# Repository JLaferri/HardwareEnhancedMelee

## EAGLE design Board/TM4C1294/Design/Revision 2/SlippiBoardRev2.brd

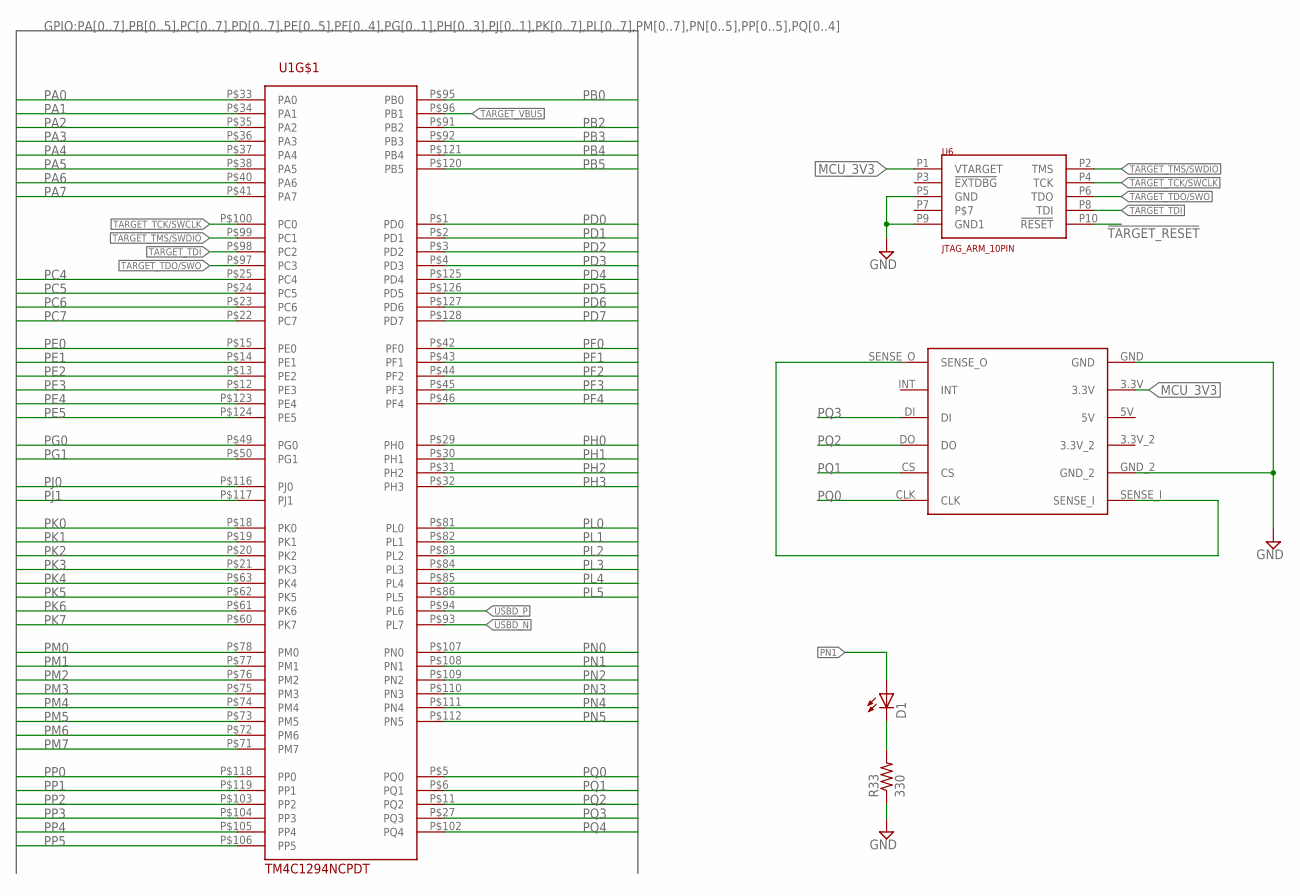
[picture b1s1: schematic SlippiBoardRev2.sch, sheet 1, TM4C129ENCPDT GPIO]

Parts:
D1: LEDCHIPLED_0603; CHIPLED_0603
R33: 330; R0402
U1: TM4C1294NCPDT; TQFP-128
U6: JTAG_ARM_10PIN; CON_2X5_50MIL
U$1: GC_MEMCARD_CON

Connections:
!TARGET_RESET: U6.P10 (!RESET); also elsewhere on the board
GND: R33.1, U6.P5 (GND), U6.P9 (GND1), U$1.GND, U$1.GND_2; also elsewhere on the board
MCU_3V3: U6.P1 (VTARGET), U$1.3.3V; also elsewhere on the board
unnamed: U$1.SENSE_I, U$1.SENSE_O
unnamed: D1.C, R33.2
PA0: U1.P$33 (PA0)
PA1: U1.P$34 (PA1)
PA2: U1.P$35 (PA2)
PA3: U1.P$36 (PA3)
PA4: U1.P$37 (PA4)
PA5: U1.P$38 (PA5)
PA6: U1.P$40 (PA6)
PA7: U1.P$41 (PA7)
PB0: U1.P$95 (PB0)
PB2: U1.P$91 (PB2)
PB3: U1.P$92 (PB3)
PB4: U1.P$121 (PB4)
PB5: U1.P$120 (PB5)
PC4: U1.P$25 (PC4)
PC5: U1.P$24 (PC5)
PC6: U1.P$23 (PC6)
PC7: U1.P$22 (PC7)
PD0: U1.P$1 (PD0)
PD1: U1.P$2 (PD1)
PD2: U1.P$3 (PD2)
PD3: U1.P$4 (PD3)
PD4: U1.P$125 (PD4)
PD5: U1.P$126 (PD5)
PD6: U1.P$127 (PD6)
PD7: U1.P$128 (PD7)
PE0: U1.P$15 (PE0)
PE1: U1.P$14 (PE1)
PE2: U1.P$13 (PE2)
PE3: U1.P$12 (PE3)
PE4: U1.P$123 (PE4)
PE5: U1.P$124 (PE5)
PF0: U1.P$42 (PF0)
PF1: U1.P$43 (PF1)
PF2: U1.P$44 (PF2)
PF3: U1.P$45 (PF3)
PF4: U1.P$46 (PF4)
PG0: U1.P$49 (PG0)
PG1: U1.P$50 (PG1)
PH0: U1.P$29 (PH0)
PH1: U1.P$30 (PH1)
PH2: U1.P$31 (PH2)
PH3: U1.P$32 (PH3)
PJ0: U1.P$116 (PJ0)
PJ1: U1.P$117 (PJ1)
PK0: U1.P$18 (PK0)
PK1: U1.P$19 (PK1)
PK2: U1.P$20 (PK2)
PK3: U1.P$21 (PK3)
PK4: U1.P$63 (PK4)
PK5: U1.P$62 (PK5)
PK6: U1.P$61 (PK6)
PK7: U1.P$60 (PK7)
PL0: U1.P$81 (PL0)
PL1: U1.P$82 (PL1)
PL2: U1.P$83 (PL2)
PL3: U1.P$84 (PL3)
PL4: U1.P$85 (PL4)
PL5: U1.P$86 (PL5)
PM0: U1.P$78 (PM0)
PM1: U1.P$77 (PM1)
PM2: U1.P$76 (PM2)
PM3: U1.P$75 (PM3)
PM4: U1.P$74 (PM4)
PM5: U1.P$73 (PM5)
PM6: U1.P$72 (PM6)
PM7: U1.P$71 (PM7)
PN0: U1.P$107 (PN0)
PN1: D1.A, U1.P$108 (PN1)
PN2: U1.P$109 (PN2)
PN3: U1.P$110 (PN3)
PN4: U1.P$111 (PN4)
PN5: U1.P$112 (PN5)
PP0: U1.P$118 (PP0)
PP1: U1.P$119 (PP1)
PP2: U1.P$103 (PP2)
PP3: U1.P$104 (PP3)
PP4: U1.P$105 (PP4)
PP5: U1.P$106 (PP5)
PQ0: U1.P$5 (PQ0), U$1.CLK
PQ1: U1.P$6 (PQ1), U$1.CS
PQ2: U1.P$11 (PQ2), U$1.DO
PQ3: U1.P$27 (PQ3), U$1.DI
PQ4: U1.P$102 (PQ4)
TARGET_TCK/SWCLK: U1.P$100 (PC0), U6.P4 (TCK)
TARGET_TDI: U1.P$98 (PC2), U6.P8 (TDI)
TARGET_TDO/SWO: U1.P$97 (PC3), U6.P6 (TDO)
TARGET_TMS/SWDIO: U1.P$99 (PC1), U6.P2 (TMS)
TARGET_VBUS: U1.P$96 (PB1)
USBD_N: U1.P$93 (PL7)
USBD_P: U1.P$94 (PL6)

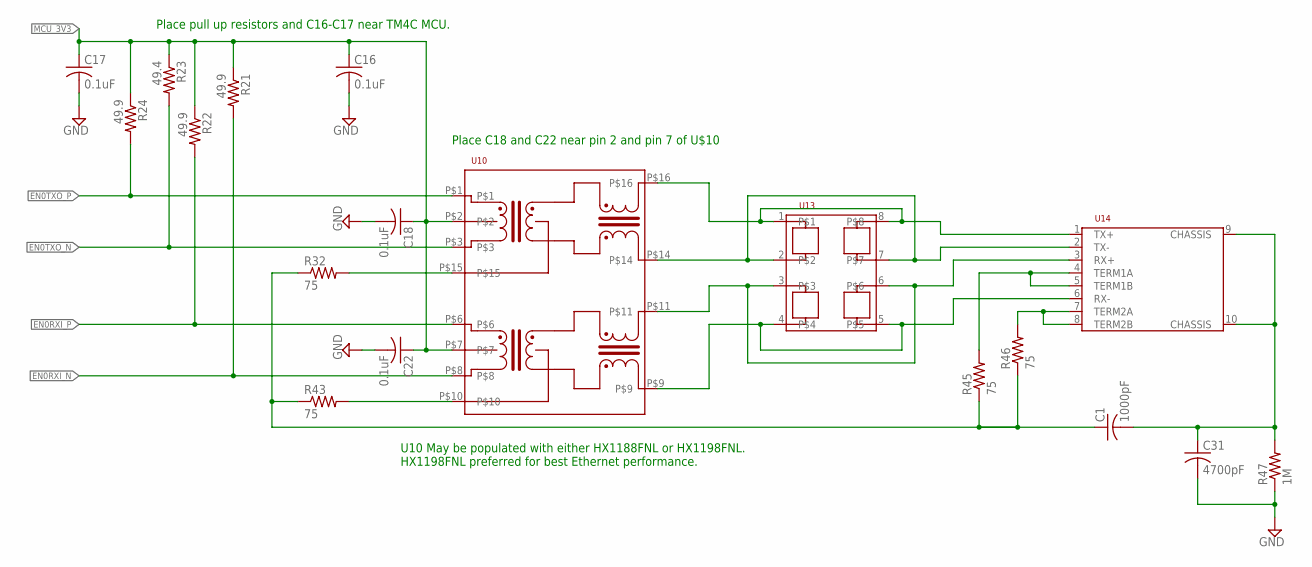
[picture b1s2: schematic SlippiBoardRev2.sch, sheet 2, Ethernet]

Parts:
C1: 1000pF; C1210
C16, C17, C18, C22: 0.1uF; C0402
C31: 4700pF; C1812
R21, R22, R24: 49.9; R0402
R23: 49.4; R0402
R32, R43, R45, R46: 75; R0402
R47: 1M; R1206
U10: MAG_PULSE_HX1188FNL
U13: SLVU2.8-4; D8
U14: JACK_RJ45_NOMAG_NOLED_TECON; RJ45_TE_CON_NOMAG_NOLED

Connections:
CHASSIS: C1.2, C31.1, R47.2, U14.9 (CHASSIS), U14.10 (CHASSIS)
EN0RXI_N: R21.2, U10.P$8; also elsewhere on the board
EN0RXI_P: R22.2, U10.P$6; also elsewhere on the board
EN0TXO_N: R23.2, U10.P$3; also elsewhere on the board
EN0TXO_P: R24.2, U10.P$1; also elsewhere on the board
GND: C16.2, C17.2, C18.2, C22.2, C31.2, R47.1; also elsewhere on the board
JACK_RX_N: U10.P$9, U13.4, U13.5, U14.6 (RX-)
JACK_RX_P: U10.P$11, U13.3, U13.6, U14.3 (RX+)
JACK_TX_N: U10.P$14, U13.2, U13.7, U14.2 (TX-)
JACK_TX_P: U10.P$16, U13.1, U13.8, U14.1 (TX+)
MCU_3V3: C16.1, C17.1, C18.1, C22.1, R21.1, R22.1, R23.1, R24.1, U10.P$2, U10.P$7; also elsewhere on the board
unnamed: R32.2, U10.P$15
unnamed: R43.2, U10.P$10
unnamed: C1.1, R32.1, R43.1, R45.1, R46.1
unnamed: R45.2, U14.4 (TERM1A), U14.5 (TERM1B)
unnamed: R46.2, U14.7 (TERM2A), U14.8 (TERM2B)

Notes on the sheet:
Place pull up resistors and C16-C17 near TM4C MCU.
Place C18 and C22 near pin 2 and pin 7 of U$10
U10 May be populated with either HX1188FNL or HX1198FNL. HX1198FNL preferred for best Ethernet performance.

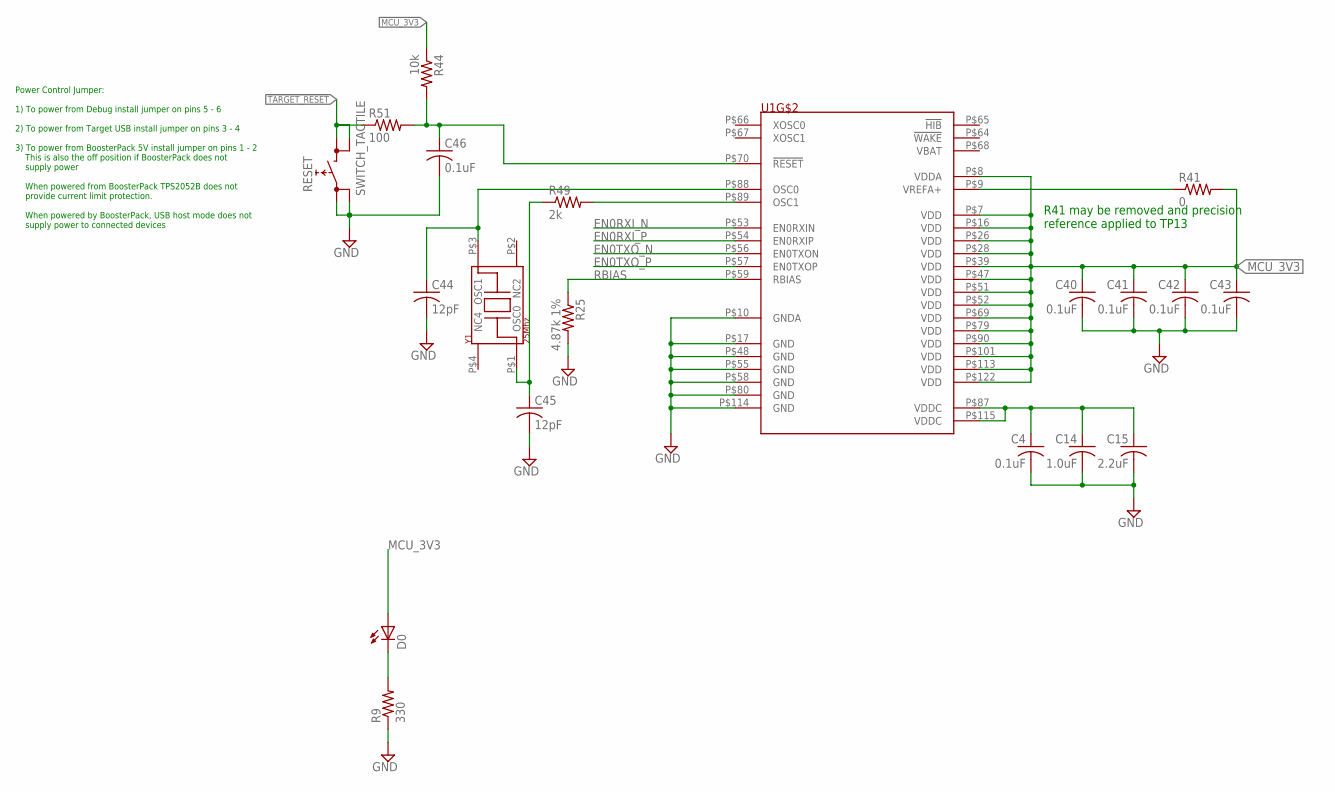
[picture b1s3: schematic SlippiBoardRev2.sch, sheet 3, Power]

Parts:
C4, C40, C41, C42, C43, C46: 0.1uF; C0402
C14: 1.0uF; C0402
C15: 2.2uF; C0603K; DIGIKEY_PARTNUM 311-1451-2-ND
C44, C45: 12pF; C0402
D0: LEDCHIPLED_0603; CHIPLED_0603
R9: 330; R0402
R25: 4.87k 1%; R0402
R41: 0; R0402
R44: 10k; R0402
R49: 2k; R0402
R51: 100; R0402
RESET: SWITCH_TACTILE; SWITCH_6MM_6MM_TE_CON_SMD
U1: TM4C1294NCPDT; TQFP-128
Y1: 25Mhz; NDK3.2X2.5

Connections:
!TARGET_RESET: R51.1, RESET.P$3 (1), RESET.P$4 (1); also elsewhere on the board
!TARGET_RESET_FILTERED: C46.1, R44.2, R51.2, U1.P$70 (!RESET)
EN0RXI_N: U1.P$53 (EN0RXIN); also elsewhere on the board
EN0RXI_P: U1.P$54 (EN0RXIP); also elsewhere on the board
EN0TXO_N: U1.P$56 (EN0TXON); also elsewhere on the board
EN0TXO_P: U1.P$57 (EN0TXOP); also elsewhere on the board
GND: C4.2, C14.2, C15.2, C40.2, C41.2, C42.2, C43.2, C44.2, C45.2, C46.2, R9.1, R25.2, RESET.P$1 (0), RESET.P$2 (0), U1.P$10 (GNDA), U1.P$17 (GND), U1.P$48 (GND), U1.P$55 (GND), U1.P$58 (GND), U1.P$80 (GND), U1.P$114 (GND); also elsewhere on the board
MCU_3V3: C40.1, C41.1, C42.1, C43.1, D0.A, R41.2, R44.1, U1.P$7 (VDD), U1.P$8 (VDDA), U1.P$16 (VDD), U1.P$26 (VDD), U1.P$28 (VDD), U1.P$39 (VDD), U1.P$47 (VDD), U1.P$51 (VDD), U1.P$52 (VDD), U1.P$69 (VDD), U1.P$79 (VDD), U1.P$90 (VDD), U1.P$101 (VDD), U1.P$113 (VDD), U1.P$122 (VDD); also elsewhere on the board
unnamed: D0.C, R9.2
unnamed: R49.2, U1.P$89 (OSC1)
unnamed: C45.1, R49.1, Y1.P$1 (OSC0)
unnamed: C44.1, U1.P$88 (OSC0), Y1.P$3 (OSC1)
RBIAS: R25.1, U1.P$59 (RBIAS)
TARGET_VDDC: C4.1, C14.1, C15.1, U1.P$87 (VDDC), U1.P$115 (VDDC)
VREF+: R41.1, U1.P$9 (VREFA+)

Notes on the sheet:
Power Control Jumper: 1) To power from Debug install jumper on pins 5 - 6 2) To power from Target USB install jumper on pins 3 - 4 3) To power from BoosterPack 5V install jumper on pins 1 - 2 This is also the off position if BoosterPack does not supply power When powered from BoosterPack TPS2052B d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
R41 may be removed and precision reference applied to TP13

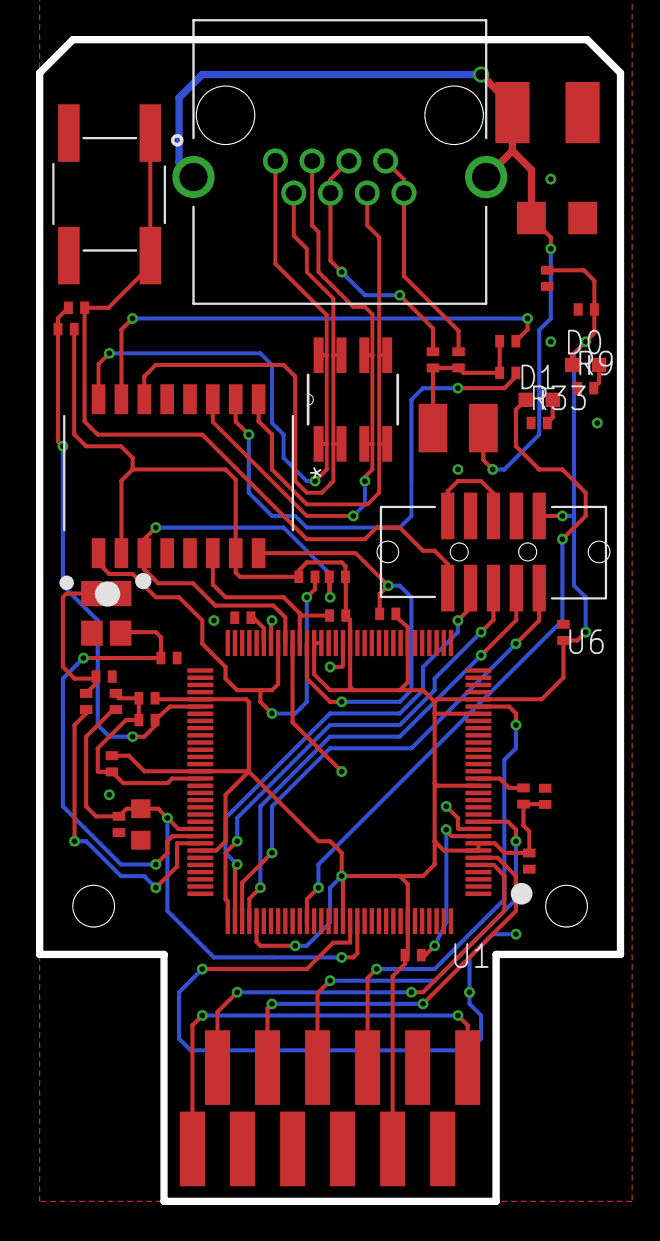
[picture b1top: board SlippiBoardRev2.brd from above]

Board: 2 copper layers, 32.3 x 64.5 mm, 42 parts (0 on the bottom side), 36 nets.

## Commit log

2015-09-05 :octocat: Added .gitattributes
2015-09-05 Added simple example asm file
2015-09-06 Event function now supports bl
2015-09-10 Created first version of ASM extraction code, added arduino source
2015-09-10 Added parallel read benchmarking
2015-09-10 continued work on arduino firmware
2015-09-11 the communication is now working flawlessly
2015-09-11 Byte reads should work now. Turns out I was assuming big endian (which was wrong)
2015-09-13 added some ethernet stuff. started working on stats calculation
2015-09-14 added stock count extraction, started statistics calculation
    issues:
    1) the end game event is getting run twice
    2) only one player is getting stats written for him
    3) last stock data not working properly
2015-09-14 added some stats, did some reformatting
2015-09-15 added some stats, fixed bugs
    Bug found:
    -Game timer starts immediately upon start of game as opposed to waiting
    for the freeze time.
2015-09-15 fixed timer bug
2015-09-15 Added recovery statistic
2015-09-16 Working version using only one Gecko Code
2015-09-16 fixed a couple bugs
    -fixed regression bug where freeze frames would be sent as updates
    -fixed issue where stock count could never be zero
2015-09-16 Added APM statistic version 1
    I expect this will be changed in the future
2015-09-17 Improved APM calculation
2015-09-17 added combo string statistic
2015-09-18 fixed bugs, added TCP server
2015-09-23 Fixed sheik/zelda bug. working on parser. finished writing server
2015-09-25 modified parse program to handle a pre-modified file instead
2015-10-14 Fixed formatting issues and added comments
2015-11-07 Added source code for TM4C1294XL firmware
2015-11-07 Fixed some recovery bugs. Added SSI3DMASlave driver files to directory
2015-11-09 last animation ID in stock stats now correctly stores the death direction/type
2015-11-09 Started work on supporting writes back to console
2015-12-08 Started work on UDP device configuration
2015-12-16 Added configuration tool and board design
2015-12-16 Improved Configuration tool GUI appearance
2015-12-17 Added proper board files
2015-12-17 Added IP validation (still slow)
2015-12-18 Added testudpconfig source
2015-12-18 Added EEPROM settings
2016-01-05 Working on implementing a server in Slippi tool
2016-01-05 Added ability to flash from config app. MAC address now gets loaded from the USERReg configuration
2016-01-06 Currently experiencing a deadlock trying to add new devices to list
2016-01-06 In the process of porting more stats code (this commit does not compile)
2016-01-08 Data is now being read correctly from game
2016-01-11 Added edgeguarding and combo strings. Now saves game output file
2016-01-13 Fixed APM calculation bug
2016-01-16 ComboString updates are now done live
2016-01-29 adds ip commit ability and EEPROM saving
2016-10-30 Adds version of code that executes a post request to a server with game summaries
2016-10-31 Only pushes out games that have been monitored since the begining
2016-10-31 Added combo string info and edgeguard info
2016-11-07 Improves memory management? Changes stock fields for consistency
2016-11-23 Adds ability to debug responses from the server
2017-02-20 Adds template support for web messages
2017-02-22 Adds support for Punishes and Sheik/Zelda detection
2017-07-04 Now outputs frame data for negative frames
2022-07-12 add rev2 board design and gci
